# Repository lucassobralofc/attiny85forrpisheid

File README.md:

# attiny85forrpisheid
a duinocoin miner

**Routing Prosses**

**Sqematics**

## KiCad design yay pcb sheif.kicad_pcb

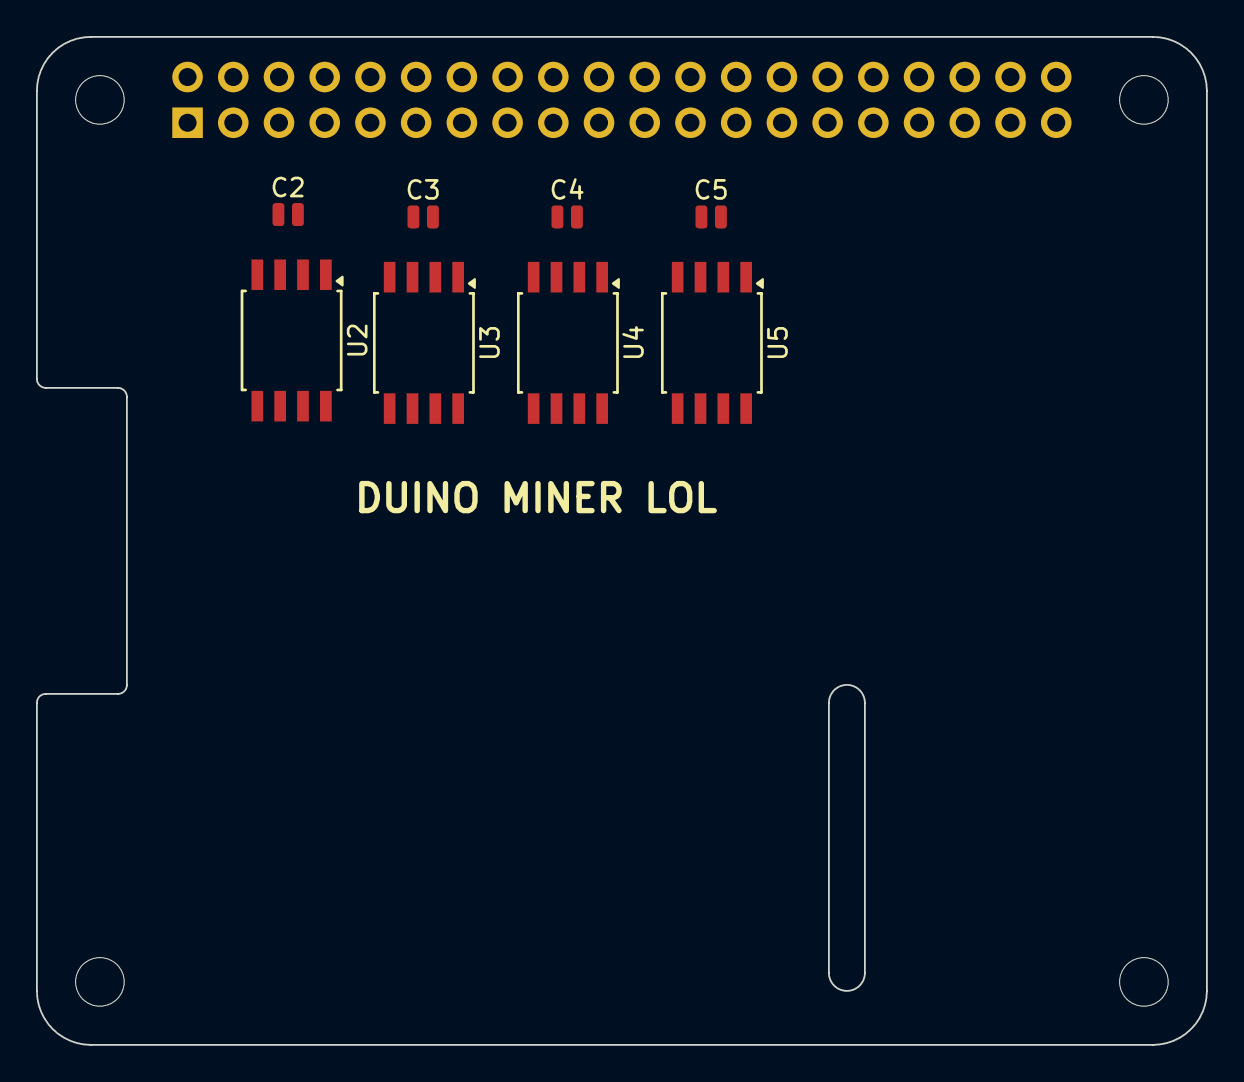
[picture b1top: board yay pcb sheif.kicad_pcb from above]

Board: 2 copper layers, 65.0 x 56.0 mm, 13 parts (1 on the bottom side), 5 nets, no tracks yet.

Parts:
C2, C3, C4, C5: C; C_0504_1310Metric
J1: GPIO; PinSocket_2x20_P2.54mm_Vertical
MH1, MH2, MH3, MH4: MountingHole_2.7mm_M2.5
U2, U3, U4, U5: ATtiny85V-10S; SOIC-8W_5.3x5.3mm_P1.27mm

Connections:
+3V3: C2.1, C3.1, C4.1, C5.1, J1.1, J1.17, U2.8 (VCC), U3.8 (VCC), U4.8 (VCC), U5.8 (VCC)
+5V: J1.2, J1.4
/GPIO2/SDA1: J1.3, U2.5 (AREF/PB0), U3.5 (AREF/PB0), U4.5 (AREF/PB0), U5.5 (AREF/PB0)
/GPIO3/SCL1: J1.5, U2.7 (PB2), U3.7 (PB2), U4.7 (PB2), U5.7 (PB2)
GND: C2.2, C3.2, C4.2, C5.2, J1.6, J1.9, J1.14, J1.20, J1.25, J1.30, J1.34, J1.39, U2.4 (GND), U3.4 (GND), U4.4 (GND), U5.4 (GND)
